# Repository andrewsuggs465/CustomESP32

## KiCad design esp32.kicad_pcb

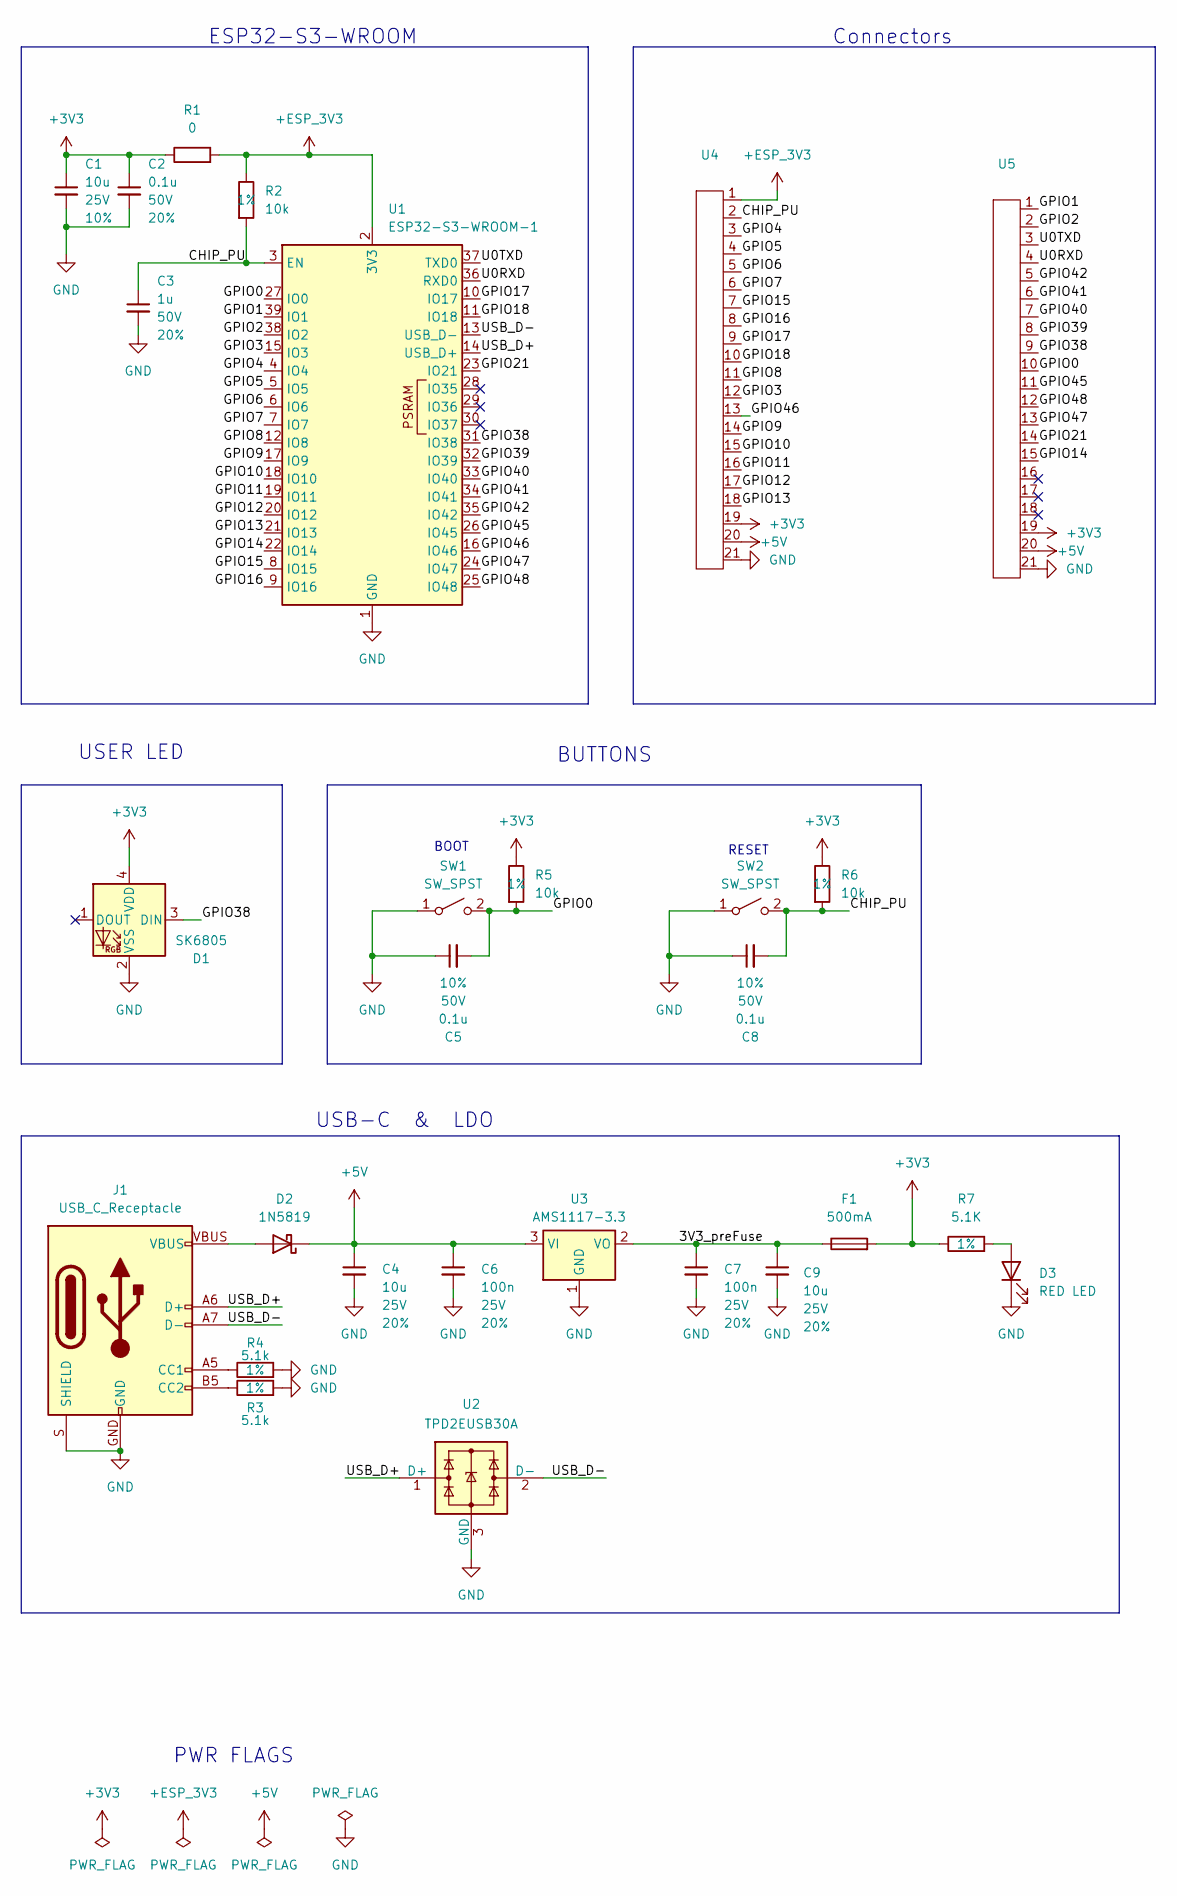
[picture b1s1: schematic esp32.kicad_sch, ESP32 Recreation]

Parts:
C1: 10u; C_0805_2012Metric; Voltage 25V; Tolerance 10%
C2: 0.1u; C_0603_1608Metric; Voltage 50V; Tolerance 20%
C3: 1u; C_0603_1608Metric; Voltage 50V; Tolerance 20%
C4, C9: 10u; C_0805_2012Metric; Voltage 25V; Tolerance 20%
C5, C8: 0.1u; C_0603_1608Metric; Voltage 50V; Tolerance 10%
C6: 100n; C_0805_2012Metric; Voltage 25V; Tolerance 20%
C7: 100n; C_0603_1608Metric; Voltage 25V; Tolerance 20%
D1: SK6805; WS2812_5050-4Pin
D2: 1N5819; D_SOD-123
D3: RED LED; LED_1206_3216Metric
F1: 500mA; Fuse_0603_1608Metric_Pad1.05x0.95mm_HandSolder
J1: USB_C_Receptacle; USB-C_16
R1: 0; R_0603_1608Metric
R2, R5, R6: 10k; R_0603_1608Metric; Tolerance 1%
R3, R4: 5.1k; R_0603_1608Metric; Tolerance 1%
R7: 5.1K; R_0603_1608Metric; Tolerance 1%
SW1, SW2: SW_SPST; 4.2x3.2mm spst switch thickness 2.5mm
U1: ESP32-S3-WROOM-1
U2: TPD2EUSB30A; Texas_DRT-3
U3: AMS1117-3.3; SOT-223-3_TabPin2
U4, U5: 1x21_pin_header

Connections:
+3V3: C1.1, C2.1, D1.4 (VDD), F1.2, R1.1, R5.1, R6.1, R7.1, U4.19, U5.19
+5V: C4.1, C6.1, D2.1 (K), U3.3 (VI), U4.20, U5.20
+ESP_3V3: R1.2, R2.1, U1.2 (3V3), U4.1
/3V3_preFuse: C7.1, C9.1, F1.1, U3.2 (VO)
/CHIP_PU: C3.1, C8.2, R2.2, R6.2, SW2.2 (B), U1.3 (EN), U4.2
/GPIO0: C5.2, R5.2, SW1.2 (B), U1.27 (IO0), U5.10
/GPIO1: U1.39 (IO1), U5.1
/GPIO2: U1.38 (IO2), U5.2
/GPIO3: U1.15 (IO3), U4.12
/GPIO4: U1.4 (IO4), U4.3
/GPIO5: U1.5 (IO5), U4.4
/GPIO6: U1.6 (IO6), U4.5
/GPIO7: U1.7 (IO7), U4.6
/GPIO8: U1.12 (IO8), U4.11
/GPIO9: U1.17 (IO9), U4.14
/GPIO10: U1.18 (IO10), U4.15
/GPIO11: U1.19 (IO11), U4.16
/GPIO12: U1.20 (IO12), U4.17
/GPIO13: U1.21 (IO13), U4.18
/GPIO14: U1.22 (IO14), U5.15
/GPIO15: U1.8 (IO15), U4.7
/GPIO16: U1.9 (IO16), U4.8
/GPIO17: U1.10 (IO17), U4.9
/GPIO18: U1.11 (IO18), U4.10
/GPIO21: U1.23 (IO21), U5.14
/GPIO38: D1.3 (DIN), U1.31 (IO38), U5.9
/GPIO39: U1.32 (IO39), U5.8
/GPIO40: U1.33 (IO40), U5.7
/GPIO41: U1.34 (IO41), U5.6
/GPIO42: U1.35 (IO42), U5.5
/GPIO45: U1.26 (IO45), U5.11
/GPIO46: U1.16 (IO46), U4.13
/GPIO47: U1.24 (IO47), U5.13
/GPIO48: U1.25 (IO48), U5.12
/U0RXD: U1.36 (RXD0), U5.4
/U0TXD: U1.37 (TXD0), U5.3
/USB_D+: J1.A6 (D+), J1.B6 (D+), U1.14 (USB_D+), U2.1 (D+)
/USB_D-: J1.A7 (D-), J1.B7 (D-), U1.13 (USB_D-), U2.2 (D-)
GND: C1.2, C2.2, C3.2, C4.2, C5.1, C6.2, C7.2, C8.1, C9.2, D1.2 (VSS), D3.1 (K), J1.GND, J1.S (SHIELD), R3.2, R4.2, SW1.1 (A), SW2.1 (A), U1.1 (GND), U1.40 (GND), U1.41 (GND), U2.3 (GND), U3.1 (GND), U4.21, U5.21
unnamed: D2.2 (A), J1.VBUS
unnamed: D3.2 (A), R7.2
unnamed: J1.A5 (CC1), R3.1
unnamed: J1.B5 (CC2), R4.1

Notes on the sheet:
ESP32-S3-WROOM
Connectors
USB-C & LDO
BUTTONS
PWR FLAGS
BOOT
RESET
USER LED

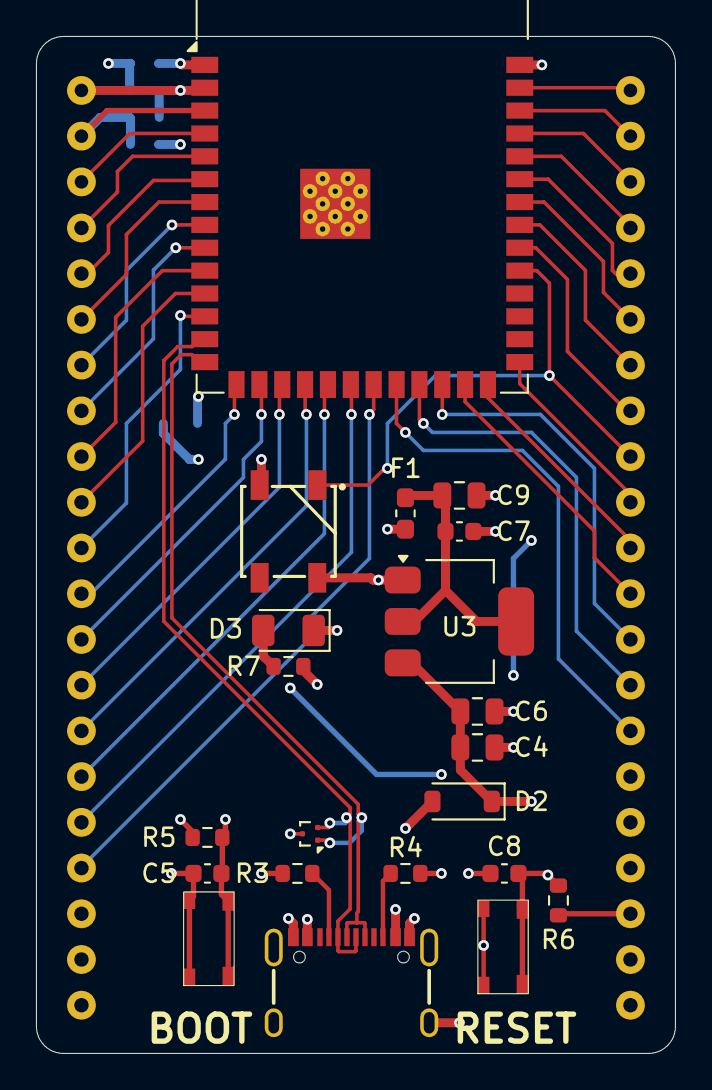
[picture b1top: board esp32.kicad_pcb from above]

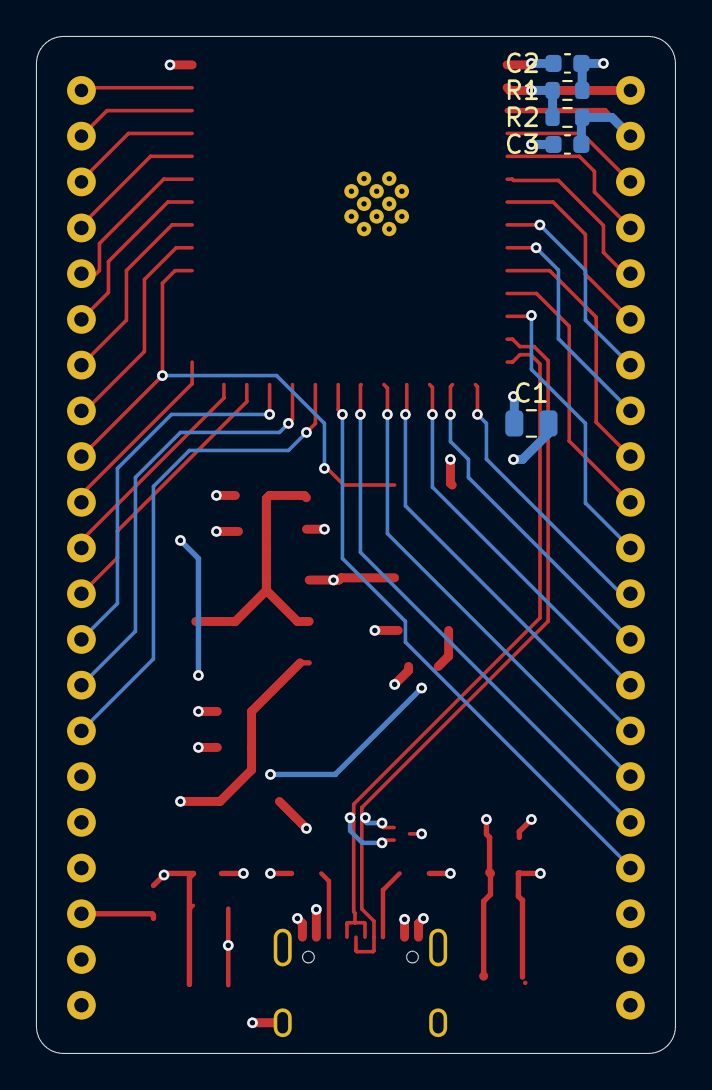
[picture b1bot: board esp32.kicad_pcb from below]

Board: 4 copper layers, 35.5 x 56.5 mm, 28 parts (5 on the bottom side), 43 nets.
